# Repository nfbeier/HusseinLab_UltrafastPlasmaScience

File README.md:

---
Repository Description: 'Last Edited: July 29, 2025'
---

# Overview

Github repository for hardware and software interfacing of the smart system used by the Hussein Ultrafast Plasma Science group at the University of Alberta for experiments LIBS and high-repetition-rate, femtosecond laser experiments.

The smart system aims to interface a collection of hardware components necessary to perform high intensity laser-plasma interactions including FLIR Blackfly CCD, Newport XPS-D8 Motion Controller,
Agilent XGS-600 Vacuum Controller, Andor iKon-M Vacuum X-ray CCD, and more. The various equipment will be controlled using Python code, and be designed in a modular structure to allow for quick
changes in experimental setups.

# Python Version
We are standardized on Python 3.10 for all software in this repo. However, usage of the LIBS code with Stellarnet spectrometers requires Python 3.8

# Importing Driver Code
This project aims to provide a consistent and reliable way to handle relative imports across various modules. By including a default pathing block at the top of the main programs, we ensure that all relative imports are correctly resolved, preventing potential import errors.

## Default Pathing Block
To maintain consistent relative imports, we include the following default pathing block at the top of our main programs:

```
import os
import sys

cwd = os.getcwd()
if "HusseinLab_UltrafastPlasmaScience" not in cwd.split(os.path.sep):
    raise ValueError("The directory does not contain 'HusseinLab_UltrafastPlasmaScience' folder.")
# Rebuild the directory string up to and including 'HusseinLab_UltrafastPlasmaScience', prevent import errors
cwd = os.path.sep.join(
    cwd.split(os.path.sep)[: cwd.split(os.path.sep).index("HusseinLab_UltrafastPlasmaScience") + 1]
)
sys.path.insert(0, cwd)
```

# Contributing
* Branches
	* Branches must change  or implement one feature
	* Branches created from branches must be merged in the order they are created
* Branch Naming
	* Branches are named as follows: <name_of_author>/<branch_type>/<description_of_branch>
	* Branch types may be one of the following: {hotfix,bugfix,experimental,feature}
* Commit Messages
	* __Do not assume your code is self explanatory__
	* __Do not assume everyone else knows what you are working on__
	* Use the imperative mood in the subject line
	* When in doubt, use the KISS method: Keep It Simple, Silly

## Converting PyQt5 Designer Files
To convert PyQt5 Designer `.ui` files to Python `.py` files that can be imported into your software, you can use the `pyuic5` tool. This tool is part of the PyQt5 package and allows you to generate Python code from the `.ui` files created using the Qt Designer.

### Command
The basic command to convert a `.ui` file to a `.py` file is:

```
pyuic5 -x ui_file.ui -o out_file.py
```

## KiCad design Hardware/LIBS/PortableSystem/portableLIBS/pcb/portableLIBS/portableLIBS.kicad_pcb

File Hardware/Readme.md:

Currently four projects are in active development

# Viron Laser System

Development of communication protocal to control the Quantel Viron Laser System for Portable LIBS.

-- Developed by Liam Droog and Shubho Mohajan 

# LIBS

Controls for automated laser-induced breakdown spectroscopy (LIBS) experiments. Communication between Stanford trigger box, Stellarnet and Thorlabs spectrometers, and linear translation stages.

-- Developed by Shubho Mohajan and Ying Wan

# Newport XPS

Development of linear translation stations controlled by the Newport XPS D4 system.

-- Developed by Nick Beier

# Tektronix TBS2000B Oscilloscope
Communication with a TBS2000B oscilloscope to read out nanosecond pulse pulse shape and energy information from a photodiode during experiments

---
Repository Description: 'Last Edited: 2024-08-28'
---

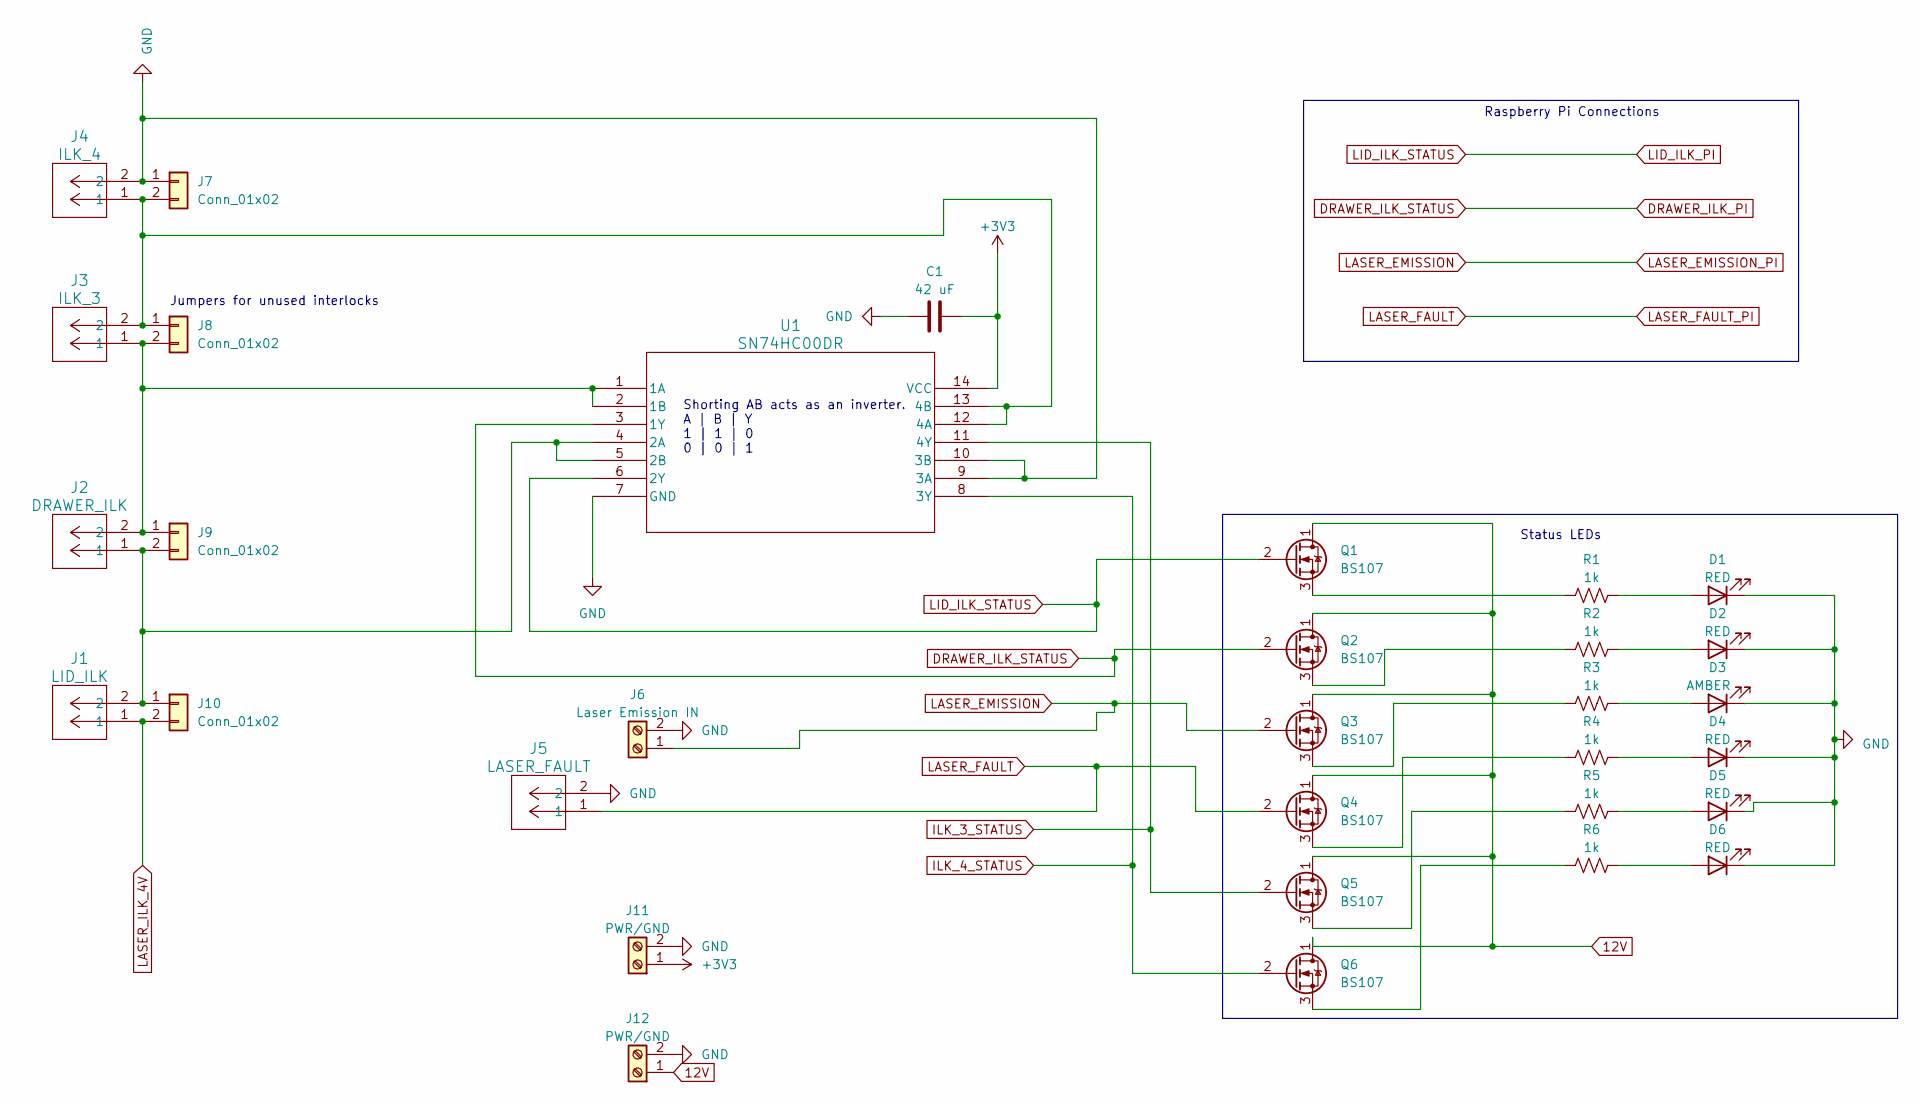
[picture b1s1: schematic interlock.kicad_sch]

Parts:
C1: 42 uF; CP_Radial_D5.0mm_P2.50mm
D1, D2, D4, D5, D6: RED; TerminalBlock_Altech_AK300-2_P5.00mm
D3: AMBER; TerminalBlock_Altech_AK300-2_P5.00mm
J1: LID_ILK; CONN_CONBN_LNX
J2: DRAWER_ILK; CONN_CONBN_LNX
J3: ILK_3; CONN_CONBN_LNX
J4: ILK_4; CONN_CONBN_LNX
J5: LASER_FAULT; CONN_CONBN_LNX
J6: Laser Emission IN; TerminalBlock_Altech_AK300-2_P5.00mm
J7, J8, J9, J10: Conn_01x02; PinHeader_1x02_P2.54mm_Vertical
J11, J12: PWR/GND; TerminalBlock_Altech_AK300-2_P5.00mm
Q1, Q2, Q3, Q4, Q5, Q6: BS107; TO-92_Inline
R1, R2, R3, R4, R5, R6: 1k; R_Axial_DIN0207_L6.3mm_D2.5mm_P7.62mm_Horizontal
U1: SN74HC00DR; DIP-14_W7.62mm_LongPads

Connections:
12V: J12.1, Q1.1 (D), Q2.1 (D), Q3.1 (D), Q4.1 (D), Q5.1 (D), Q6.1 (D)
+3V3: C1.2, J11.1, U1.14 (VCC)
DRAWER_ILK_PI: Q2.2 (G), U1.3 (1Y)
GND: C1.1, D1.1 (K), D2.1 (K), D3.1 (K), D4.1 (K), D5.1 (K), D6.1 (K), J4.2, J5.2, J6.2, J7.1, J11.2, J12.2, U1.7 (GND), U1.9 (3A), U1.10 (3B)
ILK_3_STATUS: Q5.2 (G), U1.11 (4Y)
ILK_4_STATUS: Q6.2 (G), U1.8 (3Y)
LASER_EMISSION: J6.1, Q3.2 (G)
LASER_FAULT: J5.1, Q4.2 (G)
LASER_ILK_4V: J1.1, J10.2
LID_ILK_PI: Q1.2 (G), U1.6 (2Y)
unnamed: D1.2 (A), R1.2
unnamed: D2.2 (A), R2.2
unnamed: D3.2 (A), R3.2
unnamed: D4.2 (A), R4.2
unnamed: D5.2 (A), R5.2
unnamed: D6.2 (A), R6.2
unnamed: J3.2, J4.1, J7.2, J8.1, U1.12 (4A), U1.13 (4B)
unnamed: J2.2, J3.1, J8.2, J9.1, U1.1 (1A), U1.2 (1B)
unnamed: J1.2, J2.1, J9.2, J10.1, U1.4 (2A), U1.5 (2B)
unnamed: Q1.3 (S), R1.1
unnamed: Q2.3 (S), R2.1
unnamed: Q3.3 (S), R3.1
unnamed: Q4.3 (S), R4.1
unnamed: Q5.3 (S), R5.1
unnamed: Q6.3 (S), R6.1

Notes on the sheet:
Status LEDs
Shorting AB acts as an inverter. A | B | Y 1 | 1 | 0 0 | 0 | 1
Raspberry Pi Connections
Jumpers for unused interlocks

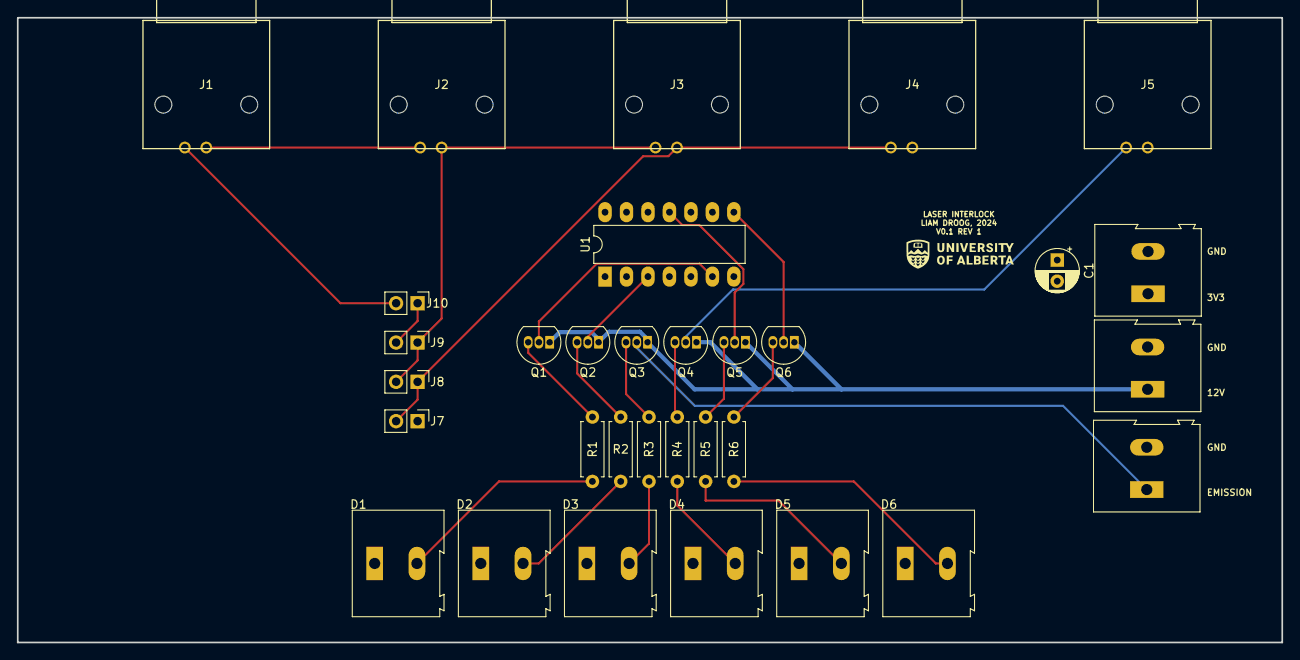
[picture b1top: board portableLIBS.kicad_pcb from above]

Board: 2 copper layers, 149.6 x 73.9 mm, 32 parts (0 on the bottom side), 25 nets.

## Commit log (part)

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2022-06-07 initial import
2022-06-08 Changed the file name
2022-06-08 bugs in metedata solved
2022-08-03 LIBSGUI with 2-axes stage control
2022-08-15 GitBook: No commit message
2022-08-23 Fixed file
    I accidently uploaded an antiquated version
2022-08-26 Uploaded newest version
    accidentally originally uploaded an antiquated version
2022-08-26 GitBook: [#1] No subject
2022-08-29 GitBook: [#2] No subject
2022-08-29 GitBook: [#3] No subject
2022-08-29 GitBook: [#4] No subject
2022-08-31 added link to documentation site
2022-10-11 Reorganization of file locations and addition of XPS code
    Reorganized and consolidated the LIBS GUI folder locations into one folder. Added the XPS code written by Ying.
2022-10-11 Further reorganization of the github
    Moved most files related to LIBS GUI into a separate folder
2022-10-11 Rename SUMMARY.md to README.md
2022-10-11 Implementation of LIBS GUI V2 as written by Ying Wan
    Updated the LIBS code section to only have a single LIBS folder with the most up-to-date version of the LIBS GUI. Subsequent versions should be stored as tags and not new folders in the github
2023-02-07 Update simulator.py
    Adding support for variable density from Bassam's code
2023-02-24 updated importer to support new scram tables.
    Changed the structure to a class.
    - class has attributes: meta_data, attributes (list of attributes), j_table, k_table, en (energy axis), j (interp. obj), and k (interp obj.)
    import tables, construct 4D matrix for each combination of ne, Te, tauR, return interpolator objects for use in the emission modelling class
2023-02-24 SCRAM Table file
    use this file as the argument of the SCRAM class in the importer.py module
2023-04-24 different version of LIBS GUI
    Add: 3 spectrometers, XPS, and Ocilloscope
2023-06-21 Viron Base Class Upload
    The base class used to communicate with the Viron laser over Telnet. Simple commands such as send_command and the sequence to take the laser from off to firing have been included.
2023-11-16 Added new spectrometers 190-800 nm
    Added new spectrometers, solved the spectrometers random connection problem, added option for not taking half step before first shot, added safety statement
2023-11-30 Oscilloscope data acquisition
    The GUI is designed to save data from two channels of Tektronix TBS2000B automatically when it triggered.
2023-11-30 Reorganization of file systems
    Reorganized the file system into software and hardware focused programs. Moved data acquisition and betatron machine learning code into the github for easy access
2024-01-12 migrate from old branch
2024-01-12 Adjust control flow and maybe enable single shot without breaking the entire gui
2024-01-12 add qspre input box and supporting code
2024-01-15 Fix qsdelay and qspre logic, tested working with Viron
2024-01-15 fix bug switching from single to auto firing
2024-01-15 add vague and unconvincing warning to tngui entry
2024-01-25 Initial GUI Development
    Setting up basic outline for the FROG gui. Including old files from Matt as a reference on how the FROG code operates
2024-01-30 Adding XPS to FROG GUI and first pass at Thorlabs code
2024-01-30 new file: Thorlabs CCS200/Thorlabs.ccs.interop64.dll new file: Thorlabs CCS200/thorlabs_ccs200.py
2024-02-08 add external fire functionality
2024-02-08 deprecate software firing and fix IP address
2024-02-08 fix reprate crash
2024-02-08 fix aesthetics
2024-02-20 Updating widget layout in the designer
    Reorganized the location of the pyFROG widgets. I'll start by using Matplotlib as the base for the plots unless pyqtgraph ends up being better
2024-02-20 Added XPS funcitonality to te FROG code. Tested with single axis and it worked as intended.
2024-02-20 Updated matplotlib figures
    Configured the plotting widgets to be approximately the correct size and orientation for FROG traces that we'd want to analyze.
2024-02-21 Added Thorlabs spectrometer thread
    Thorlabs spectrometer now acquires as a standalone thread. There is an issue with the updated integration time when the thread is running however.
2024-02-21 FROG trace implemented
    Added the code to take a FROG trace. Haven't handled saving or background yet
2024-02-21 FROG Trace Acquiring
    Successfully acquiring FROG traces. No save functionality yet, and the program hangs during the acquisition because it's not threaded properly.
2024-02-21 Messing with dual threading
2024-02-22 FROG Saving and GUI redesign
    GUI has been redesigned and improved for real-time observation of the trace being taken. The data can also now be saved as an .h5 file.
2024-02-22 Debugging sluggish GUI
2024-02-26 Redesign of the FROG threads
    Rebuilt the FROG threads to separate the Thorlabs spectrometer and XPS control into separate threads. This prevents the GUI from freezing when acquiring FROG traces. pcolormesh is being used instead 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
2024-03-07 deprecate a few features, add a few back, fix rep rate
2024-03-07 remove testing tab
2024-03-07 add warming/ready ui element
2024-03-07 fix rogue unchanged variables
2024-03-08 updated the gui code without any time sleep
2024-05-28 Initial Smart CCD Setup
    Adding code written by Shubho for FLIR cameras to a branch.
2024-07-03 Added old diagnostic GUI. Fixed pyFROG pathing
    Added the old diagnostic GUI from UCI here for reference. Fixed pathing in pyFROG
2024-07-03 Created GUI for Thorlabs Widget
    Thorlabs GUI using a format similar to the pyFROG GUI. Included MplCanvas in the folder. Resizing needs adjustment still
2024-07-03 Included saving class in Thorlabs Widget
    Thorlabs save thread copied over from UCI code. Need to switch configuration for this spectrometer. Ideally change from pandas to h5py
2024-07-11 Renaming plot from alignPlot to plot
    Made the line in the widget plot more general sounding than 'alignPlot'
2025-07-21 small file formatting changes
2025-07-21 fixed folder pathing
2025-07-21 fixed names of stages in UI to match those on the xps
    Problem with the UI_Dialog vs UI_MainWindow in the main program is preventing opening of the app
2025-07-22 fixed initialize error
    UI was updating stage information prior to selecting proper stages. Threw a key error
2025-07-22 removing lex and yacc with gitignore
2025-07-22 Cleaning up directories
2025-07-22 initial commit from main
2025-07-22 removed some old files with conflicts
2025-07-22 Moved files from Hardware into Software Folder
    pyFROG and the SolidTargetStage were moved
2025-07-22 changed lex
2025-07-22 Fixed some relative pathing and deleted old LIBS folders
2025-07-22 Renamed files for consistency
2025-07-22 jsons everywhere
2025-07-22 deleted extra copy
2025-07-22 getting rid of md files
2025-07-23 WIP delay gen
2025-07-23 WIP delay gen- more done
2025-07-23 WIP delay gen- small edits
2025-07-23 Edited on lab computer for delay generator
2025-07-23 WIP added seperate class for delay gen
2025-07-24 renamed dg645 files
2025-07-24 necessary changes to the file name and structure
2025-07-24 WIP edited the command structure for dg645
2025-07-24 WIP fixed path issues
2025-07-25 Fixed small errors
2025-07-25 WIP fixed try except blocks to print errors
2025-07-25 WIP edited to remove unecessary libraries
2025-07-27 modified .gitignore
2025-07-28 Added a load saved values option
2025-07-28 Final changes for DG645
2025-07-29 removing duplicates from separate repo
    We don't need to keep the machine learning work in this repo anymore
2025-07-29 Moving pyFROG helper files to separate folder
2025-07-30 WIP communicating with RPi
2025-07-31 Fixed code to coomunicate w Rpi
2025-08-05 WIP Solid Target Stage Control
2025-08-05 Updates to solid stage controller
2025-08-05 Update solid stage control
2025-08-07 WIP - rotation stage controls working
2025-08-07 WIP Solid Target Stage Control - DG integration
2025-08-13 WIP Solid Target Stage Control - XPS integration
2025-08-27 Migrate portableUI files
2025-08-27 move portableUI out of LIBS folder
2025-08-27 remove zip file
2025-08-27 migrate viron and ibsen hardware code to root hardware directory; modify pathing to follow
2025-08-27 actually remove viron and ibsen files from portableui folder
2026-01-16 WIP editing the delay generator to include trigger source functionality
2026-01-17 WIP editing the delay generator and limited functionality for user to only select single shot modes
2026-01-20 Tested on computer made some needed changes for program to work
2026-01-20 small issues w fdelay generator code
2026-01-20 WIP fixing ui issues for delay generator
2026-01-20 Aesthetic changes and trg src added to preliminary target stage control software
2026-01-20 Added the trigger source functionaility to the prelim solid targe tstage controller
2026-02-19 pushing changes to delay generator
2026-02-19 Changed XPS Group to correct one for FROG
    This is stupidly hard-coded into the code. I need to change this to allow us to switch actuators in the GUI
2026-02-24 Editing the GUI for better error messages
2026-02-24 Fixed GUI!!!
2026-02-24 Fixed some more gui things
2026-02-24 Fixed um to mm conversion
2026-02-24 Fixed bugs that cause false done rotation messages
2026-02-24 Fixed GUIand set proper ranges for xps stages
2026-03-10 WIP modifying linear stage controllers
2026-03-10 WIP modifying linear stage controllers-save position buttons
2026-03-12 WIP FLIR camera code
2026-03-16 FLIR Camera details
2026-03-17 Camera Code Teting - Adding Features
2026-03-17 fixed com port for actual testing
2026-03-17 testing camera
2026-03-17 Final Camera fixes : )
2026-03-18 Camera Testing Cleaning Up Output messages
2026-03-18 fixing delay gen timing
2026-03-18 com ports for dg edited
2026-04-15 WIP laser ablation control
2026-04-16 fixing da code lol
2026-04-16 WIP laser ablation control still dookie
2026-04-16 WIP laser ablation control still no g
2026-04-17 WIP laser ablation control part 2
2026-04-17 WIP laser ablation control part 3
2026-04-17 WIP laser ablation control part 4
2026-04-17 WIP laser ablation control part 5
2026-04-17 WIP laser ablation control part 6
2026-04-17 WIP laser ablation control part 7
2026-04-17 WIP laser ablation control part 8
2026-04-17 WIP Laser Ablation fixing 1D scan
2026-04-17 WIP laser ablation control part 9
2026-04-27 WIP fixed delay gen channel link issues
2026-04-28 fixing up some issues to run the exp program
2026-04-30 WIP fixing how the gui looks
2026-05-20 testing code fixes
    testing code fixes
2026-05-20 ui edited for readability
2026-05-20 Fixing rpi code
2026-05-20 Adding comments for rpm calc
2026-05-21 fixing up the server connection issue on the rpi side
2026-05-21 implementing chnages
2026-05-21 WIP fixed rel delay issues
2026-05-21 Update on delays
2026-05-22 fixing timing for single rotation
2026-05-22 WIP fixing the disconnect button
2026-05-22 WIP fixing the complete rotation button
2026-05-22 WIP fixing the shot update
2026-05-22 WIP fixing the shot update/ nshot mode
2026-05-22 delay gen inputs uopdate
2026-05-25 software updates delay values
2026-05-28 preset changes
2026-05-29 WIP adding save directory and image autosave features
2026-05-29 WIP for shifting the stage in Nshot mode
2026-06-09 minor experimental changes
2026-06-09 WIP adding error messages
2026-06-09 exp changes
2026-06-09 WIP N shot mode
2026-06-09 minor changes
2026-06-09 WIP shot mode and stage limits
2026-06-16 minor exp changes
